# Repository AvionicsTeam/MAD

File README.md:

# Projekt: Dorota Chudzik, Mikołaj Kamiński, Aleksander Dykman
## Proces prototypowania urządzeń mikrokomputerowych na przykładzie autopilota

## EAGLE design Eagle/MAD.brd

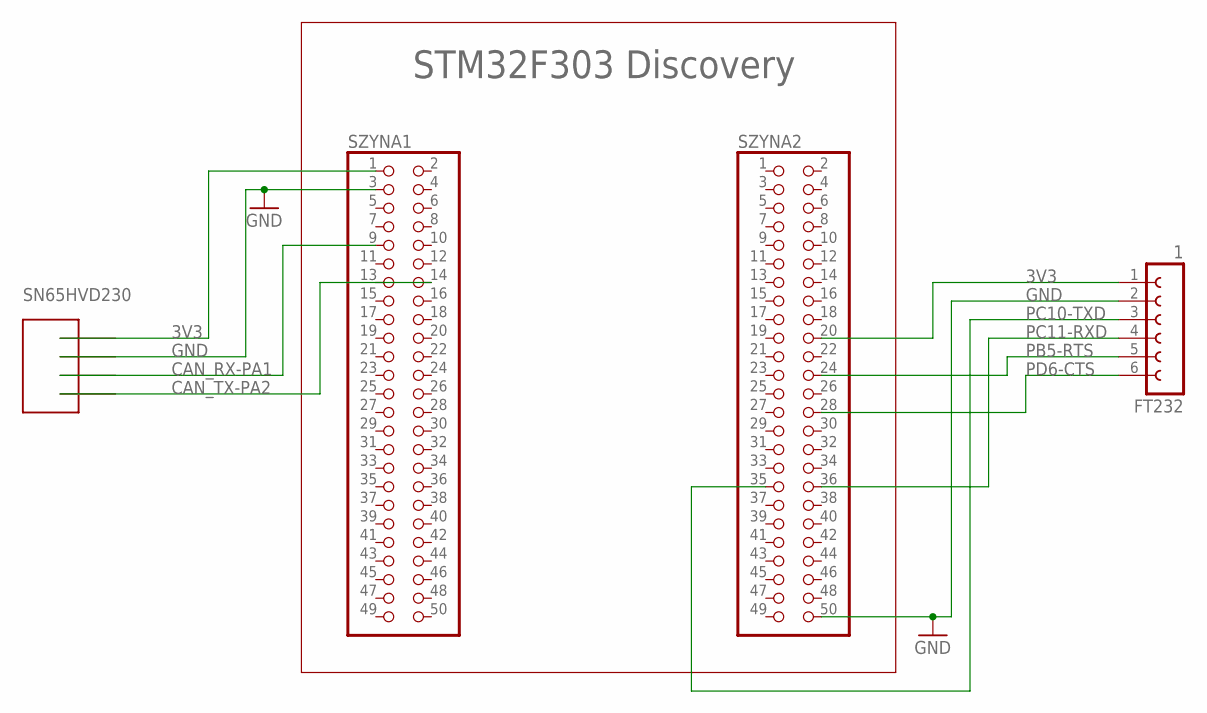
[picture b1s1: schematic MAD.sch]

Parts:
FT232: 1; FE06W
SN65HVD230: FE04W; FE04
SZYNA1, SZYNA2: PINHD-2X25; 2X25

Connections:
3V3: SN65HVD230.P$1, SZYNA1.1
3V3_2: FT232.1, SZYNA2.20
CAN_RX-PA1: SN65HVD230.P$3, SZYNA1.9
CAN_TX-PA2: SN65HVD230.P$4, SZYNA1.14
GND: FT232.2, SN65HVD230.P$2, SZYNA1.3, SZYNA2.50
PB5-RTS: FT232.5, SZYNA2.24
PC10-TXD: FT232.3, SZYNA2.35
PC11-RXD: FT232.4, SZYNA2.36
PD6-CTS: FT232.6, SZYNA2.28

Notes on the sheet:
STM32F303 Discovery
3V3
GND
CAN_RX-PA1
CAN_TX-PA2
PC10-TXD
PC11-RXD
PB5-RTS
PD6-CTS
SN65HVD230

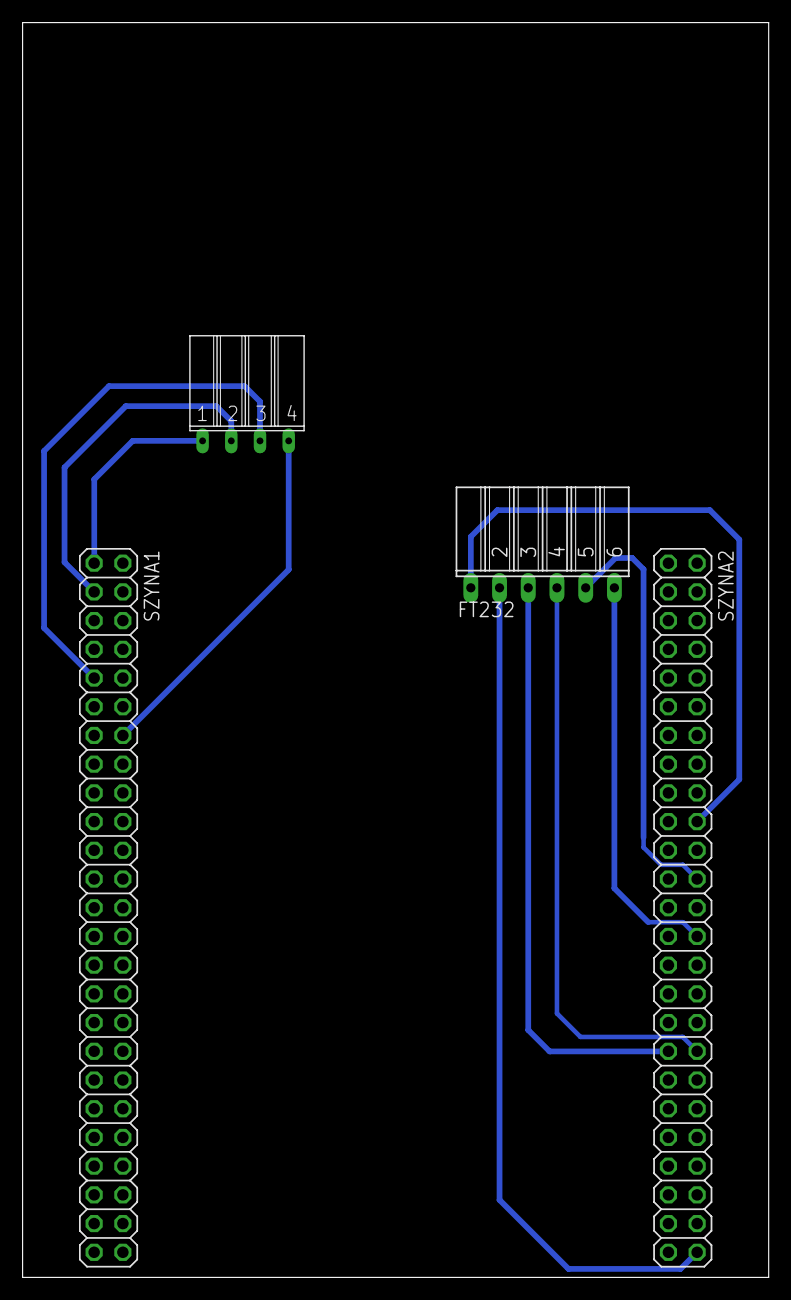
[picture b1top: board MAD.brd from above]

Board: 2 copper layers, 66.0 x 111.0 mm, 4 parts (0 on the bottom side), 9 nets.

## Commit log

2017-10-12 Dodano ogolny schemat systemu
2017-10-12 Commit testowy
2017-10-12 Alek Test
2017-10-14 Usunięto plik testowy
2017-10-24 Harmonogram
2017-10-25 Harmonogram - update Doroty
2017-10-25 Update Harmonogramu
2017-10-25 Uptade harmonogramu
2017-10-26 Dodano plik.txt
2017-10-26 Usunieto testowe pliki
2017-11-17 Aktualizacja projektu
2017-11-17 Aktualizacja opisu
2017-11-18 usunięto zbędny plik
2017-11-18 Zaktualizowany harmonogram prac
2017-11-18 Poprawa .gitignore (ignorowanie plików tymczasowych LibreOffice)
2017-11-18 Usunięto plik Założenia-Sprzęt.odt
2017-11-18 Poprawiono schemat blokowy hardware
2017-11-18 Poprawione założenia umieszczone w pliku założenia.odt
2017-11-18 Uzupełniono plik projekt.odt
2017-11-18 Uzupełnienie projektu koncepcyjnego
2017-11-18 Usunięto plik założenia.odt
2017-11-18 Dodano plik koncepcja_oprogramowania.odt
2017-11-18 Usunięto tymczasowy plik, uzupełniono plik projekt.odt w sekcji Koncepcja oprogramowania oraz przeprowadzono drobne poprawki edytorskie
2017-11-20 Dodalem dobor elementow
2017-11-22 Drobne poprawki stylistyczne w projekcie
2017-11-23 Aktualizacja harmonogramu
2017-11-23 Schemat płytki
2017-11-26 Stworzono ogólny schemat blokowy algorytmu oprogramowania
2017-11-26 Dodano schemat oprogramowania
2017-11-26 Aktualizacja
2017-12-02 dodano dokumenty do procka
2017-12-13 Aktualizacja projektu konstrukcyjnego
2017-12-13 Uzupełniono informacje o modelu matematycznym i regulatorze PID
2017-12-26 biblioteka regulatora PID
2017-12-26 aktualizacja biblioteki
2018-01-09 aktualizacja PID
2018-01-17 Created a small tool for converting data registered in X-Plane to CSV format
2018-01-17 Zarejestrowany lot w formacie MATLABa
2018-01-17 Dodano wektor czasu do zarejestrowanych danych
2018-01-17 Bug Fix: now script eliminates weird lines from CSV file
2018-01-17 Poprawiono dane w formacie MATLABa
2018-01-17 xplane2csv problem note
2018-01-17 First attempt
2018-01-17 Zaktualizowano plik matlab_workspace.mat na podstawie nowego pliku converted.csv
2018-01-17 Cleaning up the mess
2018-01-18 Added comments to xplane2csv.py file
2018-01-18 Created readme.md for xplane2csv
2018-01-23 Zaktualizowano .gitignore - ignoruje pliki Keila i MATLABa
2018-01-23 Dodano testy biblioteki PID w MATLABie
2018-01-23 Pierwsze próby stworzenia modelu matematycznego
2018-01-24 Propozycja transmitancji dla ruchu podluznego
2018-01-25 usuwam bo nie potrzebne
2018-01-25 Dodałem projekt w eaglu
2018-01-25 Utworzono projekt w Keil
2018-01-27 Aktualizacja opisu projektu
2018-01-27 Aktualizacja testów funkcji PID
2018-01-27 dodaje projekt do edycji
2018-01-27 Dodano opis testów biblioteki regulatora PID
2018-01-27 aktualizacja testów PID
2018-01-27 Revert "Poprawka konfliktu"
    This reverts commit 24b633cdea9188cd7a49479dd49add8f7b844a11, reversing
    changes made to 18022e0ff5bddd2873ad186c3db3214d73660fe6.
2018-01-27 Revert "aktualizacja testów PID"
    This reverts commit 18022e0ff5bddd2873ad186c3db3214d73660fe6.
2018-01-27 Uzupełniono projekt.odt
2018-01-27 Poprawiono skrypt wyznaczający model i opisano proces tworzenia modelu
2018-01-28 Poprawiono .gitignore tak aby Git ignorował pliki .m~
2018-01-28 Opisano po krótce do czego używaliśmy Gita
2018-01-28 dodano parę użytecznych plików
2018-01-28 usunięto niepotrzebny plik i dodano schemat w eaglu
2018-01-28 dodano opis hardware
2018-01-28 Aktualizacja opisu projektu (wstawienie nowych rozdziałów)
2018-01-28 Poprawka drobnych błędów
2018-01-28 Dodano podpisy obrazków w pliku projekt.odt
2018-01-28 Poprawiono formatowanie, fixed #8
2018-01-29 Wstawiono podsumowanie, fixed #9
2018-01-29 poprawiono błędy
2018-01-29 Dołączono projekt w formacie .pdf
